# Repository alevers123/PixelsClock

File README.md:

# PixelsClock
Seven Segment LED Clock made from Neo Pixels

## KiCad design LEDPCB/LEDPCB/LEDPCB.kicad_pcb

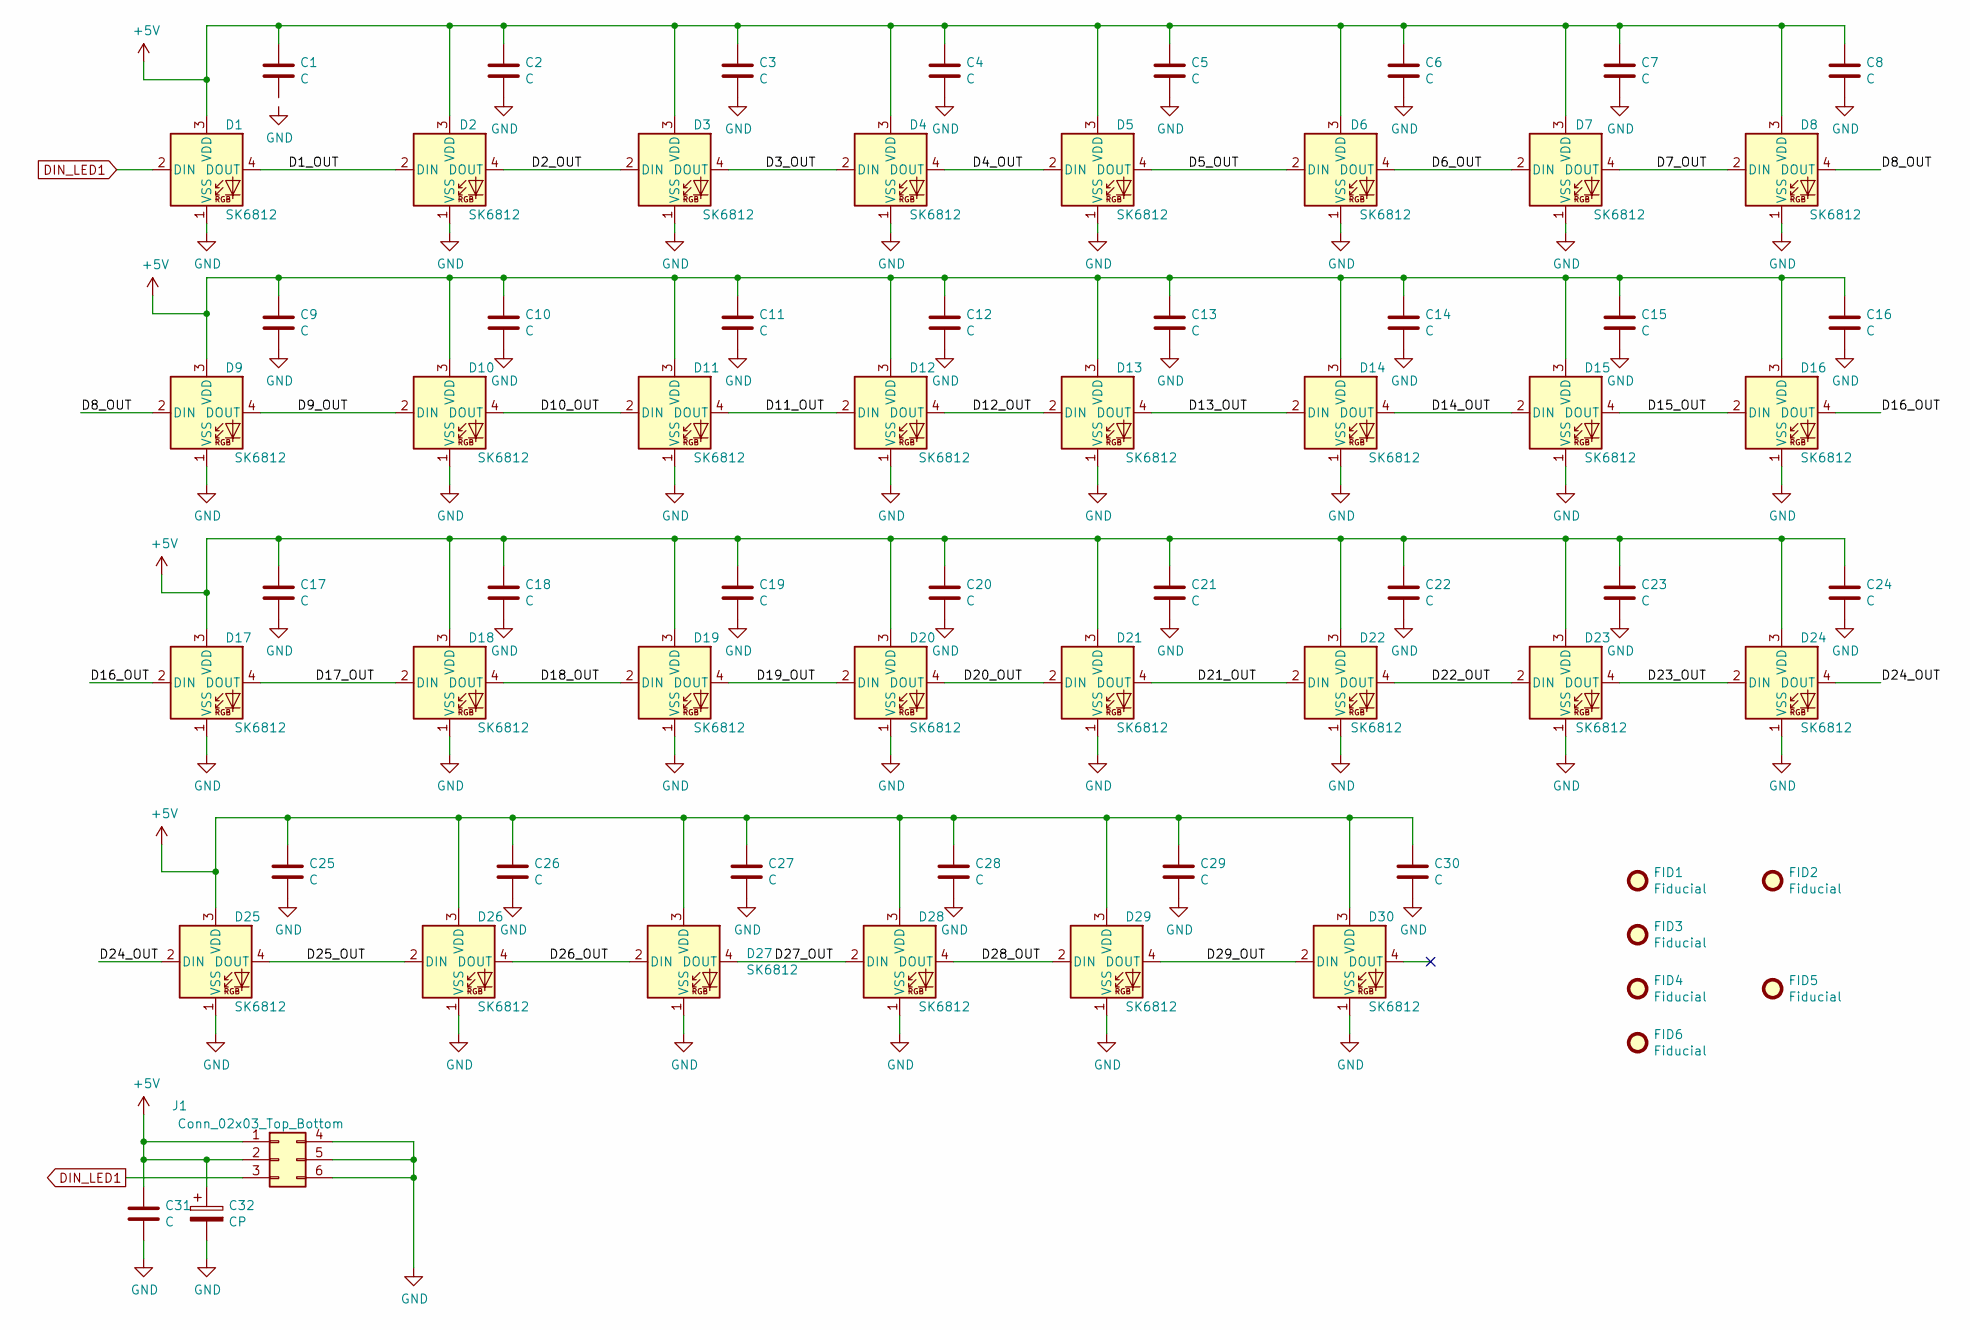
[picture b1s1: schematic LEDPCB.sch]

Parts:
C1, C2, C3, C4, C5, C6, C7, C8, C9, C10, C11, C12, C13, C14, C15, C16, C17, C18, C19, C20, C21, C22, C23, C24, C25, C26, C27, C28, C29, C30: C; C_0402_1005Metric
C31: C; C_1206_3216Metric
C32: CP; CP_EIA-6032-28_Kemet-C
D1, D2, D3, D4, D5, D6, D7, D8, D9, D10, D11, D12, D13, D14, D15, D16, D17, D18, D19, D20, D21, D22, D23, D24, D25, D26, D27, D28, D29, D30: SK6812; LED_SK6812_PLCC4_5.0x5.0mm_P3.2mm
FID1, FID2, FID3, FID4, FID5, FID6: Fiducial; Fiducial_1mm_Mask2mm
J1: Conn_02x03_Top_Bottom; PinHeader_2x03_P1.00mm_Vertical_SMD

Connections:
+5V: C1.1, C2.1, C3.1, C4.1, C5.1, C6.1, C7.1, C8.1, C9.1, C10.1, C11.1, C12.1, C13.1, C14.1, C15.1, C16.1, C17.1, C18.1, C19.1, C20.1, C21.1, C22.1, C23.1, C24.1, C25.1, C26.1, C27.1, C28.1, C29.1, C30.1, C31.1, C32.1, D1.3 (VDD), D2.3 (VDD), D3.3 (VDD), D4.3 (VDD), D5.3 (VDD), D6.3 (VDD), D7.3 (VDD), D8.3 (VDD), D9.3 (VDD), D10.3 (VDD), D11.3 (VDD), D12.3 (VDD), D13.3 (VDD), D14.3 (VDD), D15.3 (VDD), D16.3 (VDD), D17.3 (VDD), D18.3 (VDD), D19.3 (VDD), D20.3 (VDD), D21.3 (VDD), D22.3 (VDD), D23.3 (VDD), D24.3 (VDD), D25.3 (VDD), D26.3 (VDD), D27.3 (VDD), D28.3 (VDD), D29.3 (VDD), D30.3 (VDD), J1.1, J1.2
/D1_OUT: D1.4 (DOUT), D2.2 (DIN)
/D2_OUT: D2.4 (DOUT), D3.2 (DIN)
/D3_OUT: D3.4 (DOUT), D4.2 (DIN)
/D4_OUT: D4.4 (DOUT), D5.2 (DIN)
/D5_OUT: D5.4 (DOUT), D6.2 (DIN)
/D6_OUT: D6.4 (DOUT), D7.2 (DIN)
/D7_OUT: D7.4 (DOUT), D8.2 (DIN)
/D8_OUT: D8.4 (DOUT), D9.2 (DIN)
/D9_OUT: D9.4 (DOUT), D10.2 (DIN)
/D10_OUT: D10.4 (DOUT), D11.2 (DIN)
/D11_OUT: D11.4 (DOUT), D12.2 (DIN)
/D12_OUT: D12.4 (DOUT), D13.2 (DIN)
/D13_OUT: D13.4 (DOUT), D14.2 (DIN)
/D14_OUT: D14.4 (DOUT), D15.2 (DIN)
/D15_OUT: D15.4 (DOUT), D16.2 (DIN)
/D16_OUT: D16.4 (DOUT), D17.2 (DIN)
/D17_OUT: D17.4 (DOUT), D18.2 (DIN)
/D18_OUT: D18.4 (DOUT), D19.2 (DIN)
/D19_OUT: D19.4 (DOUT), D20.2 (DIN)
/D20_OUT: D20.4 (DOUT), D21.2 (DIN)
/D21_OUT: D21.4 (DOUT), D22.2 (DIN)
/D22_OUT: D22.4 (DOUT), D23.2 (DIN)
/D23_OUT: D23.4 (DOUT), D24.2 (DIN)
/D24_OUT: D24.4 (DOUT), D25.2 (DIN)
/D25_OUT: D25.4 (DOUT), D26.2 (DIN)
/D26_OUT: D26.4 (DOUT), D27.2 (DIN)
/D27_OUT: D27.4 (DOUT), D28.2 (DIN)
/D28_OUT: D28.4 (DOUT), D29.2 (DIN)
/D29_OUT: D29.4 (DOUT), D30.2 (DIN)
DIN_LED1: D1.2 (DIN), J1.3
GND: C2.2, C3.2, C4.2, C5.2, C6.2, C7.2, C8.2, C9.2, C10.2, C11.2, C12.2, C13.2, C14.2, C15.2, C16.2, C17.2, C18.2, C19.2, C20.2, C21.2, C22.2, C23.2, C24.2, C25.2, C26.2, C27.2, C28.2, C29.2, C30.2, C31.2, C32.2, D1.1 (VSS), D2.1 (VSS), D3.1 (VSS), D4.1 (VSS), D5.1 (VSS), D6.1 (VSS), D7.1 (VSS), D8.1 (VSS), D9.1 (VSS), D10.1 (VSS), D11.1 (VSS), D12.1 (VSS), D13.1 (VSS), D14.1 (VSS), D15.1 (VSS), D16.1 (VSS), D17.1 (VSS), D18.1 (VSS), D19.1 (VSS), D20.1 (VSS), D21.1 (VSS), D22.1 (VSS), D23.1 (VSS), D24.1 (VSS), D25.1 (VSS), D26.1 (VSS), D27.1 (VSS), D28.1 (VSS), D29.1 (VSS), D30.1 (VSS), J1.4, J1.5, J1.6

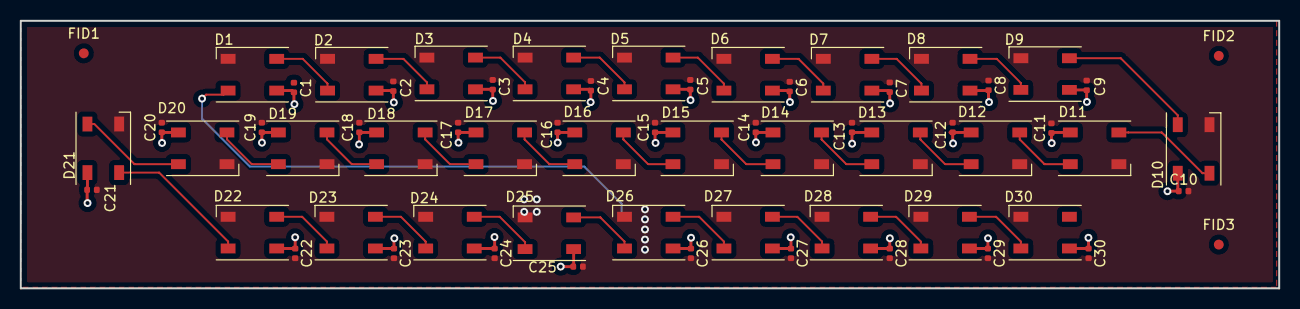
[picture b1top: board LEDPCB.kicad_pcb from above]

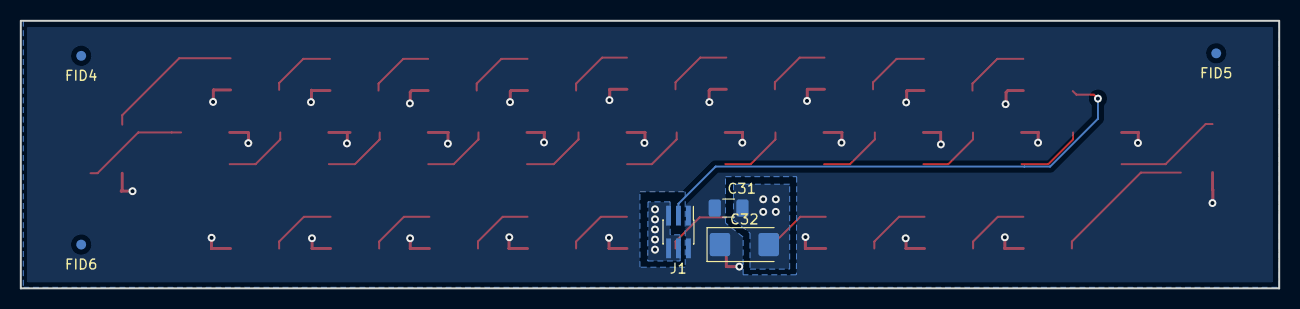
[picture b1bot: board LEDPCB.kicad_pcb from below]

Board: 2 copper layers, 127.0 x 27.0 mm, 69 parts (6 on the bottom side), 32 nets.

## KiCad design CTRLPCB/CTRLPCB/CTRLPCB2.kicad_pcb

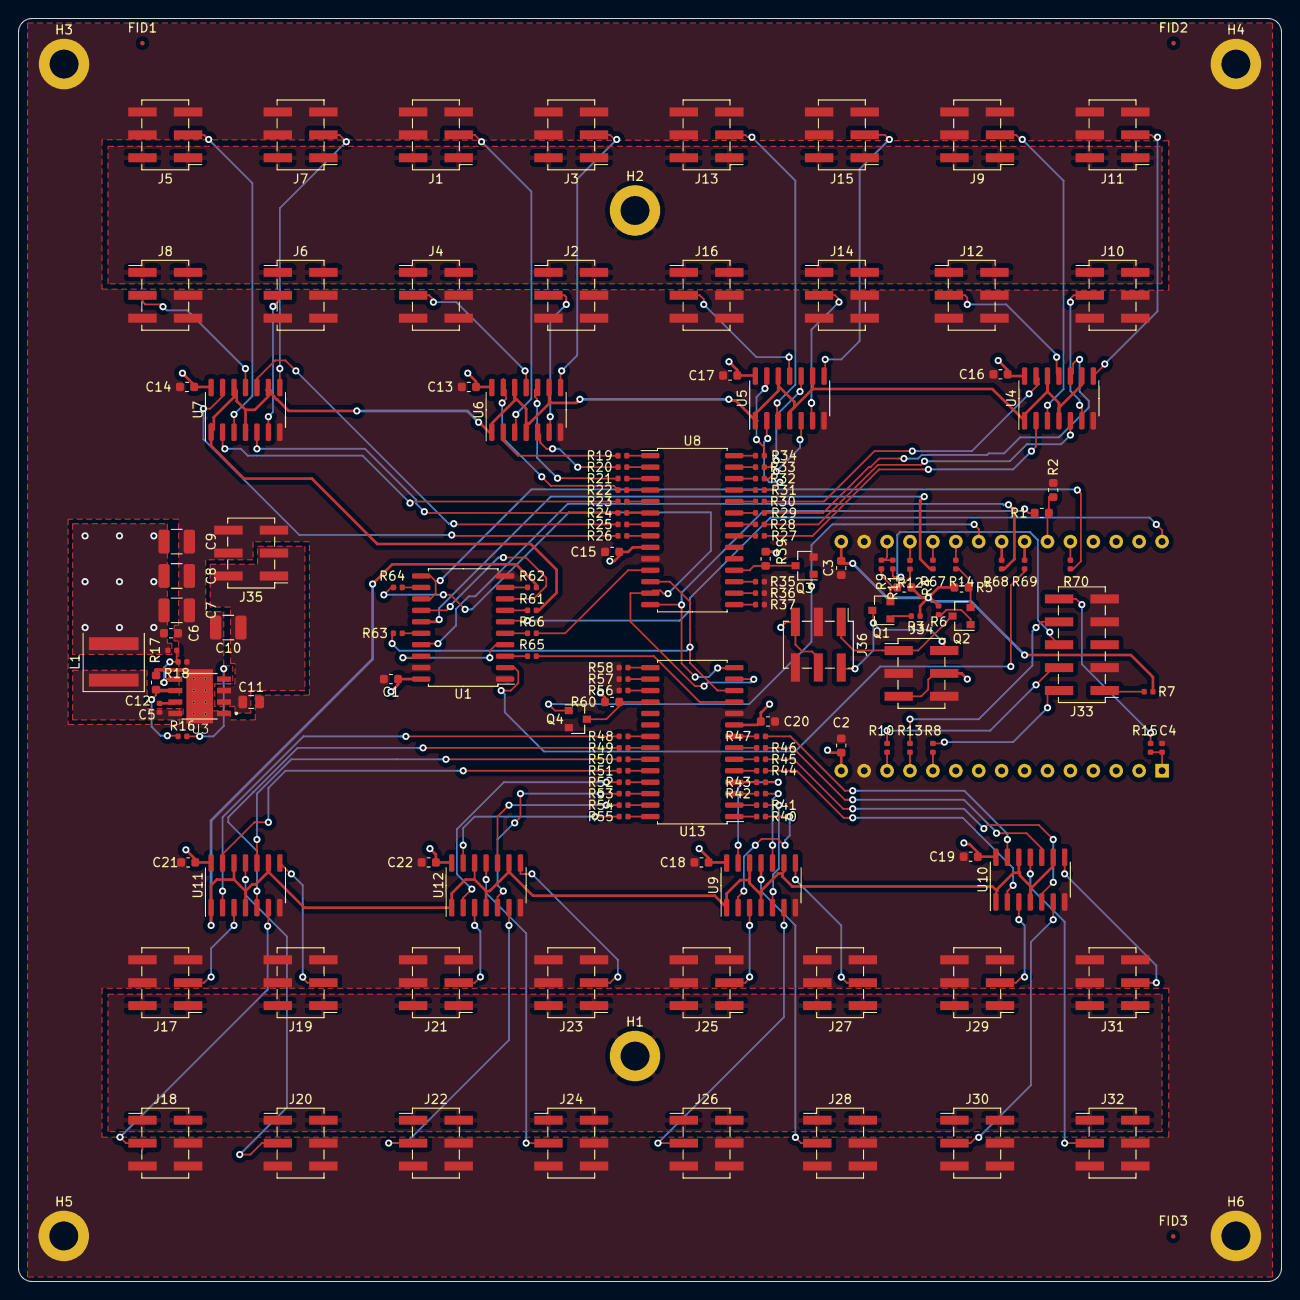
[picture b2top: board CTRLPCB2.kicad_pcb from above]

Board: 2 copper layers, 140.0 x 140.0 mm, 153 parts (1 on the bottom side), 160 nets.

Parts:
C1, C2, C3, C15, C20: C; C_0603_1608Metric
C4: C; C_0402_1005Metric
C5: 100nF; C_0402_1005Metric
C6: 100nF; C_0603_1608Metric
C7, C8, C9: C; C_1210_3225Metric
C10: 10u; C_1210_3225Metric
C11: 220n; C_0805_2012Metric
C12: 1u; C_0603_1608Metric
C13, C14, C16, C17, C18, C19, C21, C22: 100n; C_0603_1608Metric
FID1, FID2, FID3: Fiducial; Fiducial_0.5mm_Mask1.5mm
H1, H2, H3, H4, H5, H6: MountingHole_Pad; MountingHole_3.2mm_M3_DIN965_Pad
J1, J2, J3, J4, J5, J6, J7, J8, J9, J10, J11, J12, J13, J14, J15, J16, J17, J18, J19, J20, J21, J22, J23, J24, J25, J26, J27, J28, J29, J30, J31, J32, J34, J35, J36: Conn_02x03_Top_Bottom; PinHeader_2x03_P2.54mm_Vertical_SMD
J33: Conn_02x05_Odd_Even; PinHeader_2x05_P2.54mm_Vertical_SMD
L1: 10u; L_Coilcraft_XAL60xx_6.36x6.56mm
Q1, Q2, Q3, Q4: Q_NMOS_GSD; SOT-23
R1: 510R; R_0603_1608Metric
R2, R39, R60: 1k; R_0603_1608Metric
R3, R6, R7, R8, R9, R10, R11, R12, R13, R14, R15, R20, R21, R22, R23, R24, R25, R26, R27, R28, R29, R30, R31, R32, R33, R34, R36, R37, R41, R42, R43, R44, R45, R46, R47, R48, R49, R50, R51, R52, R53, R54, R55, R57, R58, R61, R62, R63, R64, R65, R66, R67, R68, R69, R70: 33R; R_0402_1005Metric
R4, R5: 2k; R_0603_1608Metric
R16, R17: 100k; R_0402_1005Metric
R18: 24.9k; R_0402_1005Metric
R19, R35, R40, R56: 33; R_0402_1005Metric
U1: 74HCT240; SOIC-20W_7.5x12.8mm_P1.27mm
U2: ESP32_DevKit_V1_DOIT; esp32_devkit_v1_doit
U3: LMR33630ADDA; NOPB
U4, U5, U6, U7, U9, U10, U11, U12: 74HC00; SOIC-14_3.9x8.7mm_P1.27mm
U8, U13: MCP23S17_SO; SOIC-28W_7.5x17.9mm_P1.27mm

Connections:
+3V3: C3.2, R3.1, R4.1, R5.1, R6.1, R7.2, U2.16
+5V: C1.1, C2.1, C6.1, C7.1, C8.1, C9.1, C13.1, C14.1, C15.1, C16.1, C17.1, C18.1, C19.1, C20.1, C21.1, C22.1, J34.4, J34.5, J36.4, J36.5, L1.2, R17.1, R39.1, R60.1, U1.20, U2.15, U4.14, U5.14, U6.14, U7.14, U8.9, U9.14, U10.14, U11.14, U12.14, U13.9
+24V: C10.1, C11.1, J35.1, J35.2, J35.3, U3.2, U3.3
/+5V_HIGH_POWER: H2.1, J1.1, J1.2, J2.1, J2.2, J3.1, J3.2, J4.1, J4.2, J5.1, J5.2, J6.1, J6.2, J7.1, J7.2, J8.1, J8.2, J9.1, J9.2, J10.1, J10.2, J11.1, J11.2, J12.1, J12.2, J13.1, J13.2, J14.1, J14.2, J15.1, J15.2, J16.1, J16.2
/+5V_HIGH_POWER_2: H1.1, J17.1, J17.2, J18.1, J18.2, J19.1, J19.2, J20.1, J20.2, J21.1, J21.2, J22.1, J22.2, J23.1, J23.2, J24.1, J24.2, J25.1, J25.2, J26.1, J26.2, J27.1, J27.2, J28.1, J28.2, J29.1, J29.2, J30.1, J30.2, J31.1, J31.2, J32.1, J32.2
/CS0: R68.1, U1.17
/CS0_INV_LEV: R65.2, U1.3
/CS0_INV_LEV_E: R65.1, U13.11
/CS1: R67.1, U1.15
/CS2_INV_LEV: R66.2, U1.5
/CS2_INV_LEV_E: R66.1, U8.11
/GPIO2: R12.2, U2.19
/GPIO4: R67.2, U2.20
/GPIO5: R68.2, U2.23
/GPIO12: R13.2, U2.12
/GPIO13: R10.2, U2.13
/GPIO14: R8.2, U2.11
/GPIO15: R9.2, R11.2, U2.18
/GPIO16: R14.2, U2.21
/GPIO18: R69.2, U2.24
/GPIO21: R70.2, U2.26
/I2C_SCL: Q2.2, R5.2, R14.1
/I2C_SDA: Q1.2, R4.2, R9.1, R12.1
/I2S_SK6812: R70.1, U1.11, U1.13
/I2S_SK6812_INV_LEV_1: R61.2, U1.7
/I2S_SK6812_INV_LEV_1_E: R61.1, U4.1, U4.4, U4.9, U4.12, U5.1, U5.4, U5.9, U5.12, U6.1, U6.4, U6.9, U6.12, U7.1, U7.4, U7.9, U7.12
/I2S_SK6812_INV_LEV_2: R62.2, U1.9
/I2S_SK6812_INV_LEV_2_E: R62.1, U9.1, U9.4, U9.9, U9.12, U10.1, U10.4, U10.9, U10.12, U11.1, U11.4, U11.9, U11.12, U12.1, U12.4, U12.9, U12.12
/MISO: R1.1, U8.14, U13.14
/MISO_LEV: R1.2, R2.1, U2.25
/MOSI: U1.6, U2.30
/MOSI_INV_LEV: U1.8, U1.14
/MOSI_LEV: R64.2, U1.12
/RESET: J33.10, R15.2
/SCK: R69.1, U1.2
/SCK_INV_LEV: U1.4, U1.18
/SCK_LEV: R63.2, U1.16
/SCK_LEV_E: R63.1, U8.12, U13.12
/SEG_BUS2_0: J17.3, U11.3
/SEG_BUS2_1: J18.3, U11.6
/SEG_BUS2_2: J19.3, U11.8
/SEG_BUS2_3: J20.3, U11.11
/SEG_BUS2_4: J21.3, U12.3
/SEG_BUS2_5: J22.3, U12.6
/SEG_BUS2_6: J23.3, U12.8
/SEG_BUS2_7: J24.3, U12.11
/SEG_BUS2_8: J25.3, U9.3
/SEG_BUS2_9: J26.3, U9.6
/SEG_BUS2_10: J27.3, U9.8
/SEG_BUS2_11: J28.3, U9.11
/SEG_BUS2_12: J29.3, U10.3
/SEG_BUS2_13: J30.3, U10.6
/SEG_BUS2_14: J31.3, U10.8
/SEG_BUS2_15: J32.3, U10.11
/SEG_BUS_0: J1.3, U6.3
/SEG_BUS_1: J2.3, U6.6
/SEG_BUS_2: J3.3, U6.8
/SEG_BUS_3: J4.3, U6.11
/SEG_BUS_4: J5.3, U7.3
/SEG_BUS_5: J6.3, U7.6
/SEG_BUS_6: J7.3, U7.8
/SEG_BUS_7: J8.3, U7.11
/SEG_BUS_8: J9.3, U4.3
/SEG_BUS_9: J10.3, U4.6
/SEG_BUS_10: J11.3, U4.8
/SEG_BUS_11: J12.3, U4.11
/SEG_BUS_12: J13.3, U5.3
/SEG_BUS_13: J14.3, U5.6
/SEG_BUS_14: J15.3, U5.8
/SEG_BUS_15: J16.3, U5.11
/Sheet5FDBBAA1_2/MOSI: R64.1, U8.13, U13.13
/Sheet5FDBBAA1_2/PA0: R19.2, U8.1
/Sheet5FDBBAA1_2/PA0_E: R19.1, U6.2
/Sheet5FDBBAA1_2/PA1: R20.2, U8.2
/Sheet5FDBBAA1_2/PA1_E: R20.1, U6.5
/Sheet5FDBBAA1_2/PA2: R21.2, U8.3
/Sheet5FDBBAA1_2/PA2_E: R21.1, U6.10
/Sheet5FDBBAA1_2/PA3: R22.2, U8.4
/Sheet5FDBBAA1_2/PA3_E: R22.1, U6.13
/Sheet5FDBBAA1_2/PA4: R23.2, U8.5
/Sheet5FDBBAA1_2/PA4_E: R23.1, U7.2
/Sheet5FDBBAA1_2/PA5: R24.2, U8.6
/Sheet5FDBBAA1_2/PA5_E: R24.1, U7.5
/Sheet5FDBBAA1_2/PA6: R25.2, U8.7
/Sheet5FDBBAA1_2/PA6_E: R25.1, U7.10
/Sheet5FDBBAA1_2/PA7: R26.2, U8.8
/Sheet5FDBBAA1_2/PA7_E: R26.1, U7.13
/Sheet5FDBBAA1_2/PB0: R27.2, U8.21
/Sheet5FDBBAA1_2/PB0_E: R27.1, U4.2
/Sheet5FDBBAA1_2/PB1: R28.2, U8.22
/Sheet5FDBBAA1_2/PB1_E: R28.1, U4.5
/Sheet5FDBBAA1_2/PB2: R29.2, U8.23
/Sheet5FDBBAA1_2/PB2_E: R29.1, U4.10
/Sheet5FDBBAA1_2/PB3: R30.2, U8.24
/Sheet5FDBBAA1_2/PB3_E: R30.1, U4.13
/Sheet5FDBBAA1_2/PB4: R31.2, U8.25
/Sheet5FDBBAA1_2/PB4_E: R31.1, U5.2
/Sheet5FDBBAA1_2/PB5: R32.2, U8.26
/Sheet5FDBBAA1_2/PB5_E: R32.1, U5.5
/Sheet5FDBBAA1_2/PB6: R33.2, U8.27
/Sheet5FDBBAA1_2/PB6_E: R33.1, U5.10
/Sheet5FDBBAA1_2/PB7: R34.2, U8.28
/Sheet5FDBBAA1_2/PB7_E: R34.1, U5.13
/Sheet5FDBBAA1_2/RESET: Q3.1, Q4.1, U2.22
/TCLK: J33.4, R10.1
/TDI: J33.8, R13.1
/TDO: J33.6, R11.1
/TMS: J33.2, R8.1
/sheet5FF17740/PA0: R48.2, U13.21
/sheet5FF17740/PA0_E: R48.1, U11.2
/sheet5FF17740/PA1: R49.2, U13.22
/sheet5FF17740/PA1_E: R49.1, U11.5
/sheet5FF17740/PA2: R50.2, U13.23
/sheet5FF17740/PA2_E: R50.1, U11.10
/sheet5FF17740/PA3: R51.2, U13.24
/sheet5FF17740/PA3_E: R51.1, U11.13
/sheet5FF17740/PA4: R52.2, U13.25
/sheet5FF17740/PA4_E: R52.1, U12.2
/sheet5FF17740/PA5: R53.2, U13.26
/sheet5FF17740/PA5_E: R53.1, U12.5
/sheet5FF17740/PA6: R54.2, U13.27
/sheet5FF17740/PA6_E: R54.1, U12.10
/sheet5FF17740/PA7: R55.2, U13.28
/sheet5FF17740/PA7_E: R55.1, U12.13
/sheet5FF17740/PB0: R40.2, U13.1
/sheet5FF17740/PB0_E: R40.1, U9.2
/sheet5FF17740/PB1: R41.2, U13.2
/sheet5FF17740/PB1_E: R41.1, U9.5
/sheet5FF17740/PB2: R42.2, U13.3
/sheet5FF17740/PB2_E: R42.1, U9.10
/sheet5FF17740/PB3: R43.2, U13.4
/sheet5FF17740/PB3_E: R43.1, U9.13
/sheet5FF17740/PB4: R44.2, U13.5
/sheet5FF17740/PB4_E: R44.1, U10.2
/sheet5FF17740/PB5: R45.2, U13.6
/sheet5FF17740/PB5_E: R45.1, U10.5
/sheet5FF17740/PB6: R46.2, U13.7
/sheet5FF17740/PB6_E: R46.1, U10.10
/sheet5FF17740/PB7: R47.2, U13.8
/sheet5FF17740/PB7_E: R47.1, U10.13
GND: C1.2, C2.2, C3.1, C4.1, C6.2, C7.2, C8.2, C9.2, C10.2, C11.2, C12.2, C13.2, C14.2, C15.2, C16.2, C17.2, C18.2, C19.2, C20.2, C21.2, C22.2, H3.1, H4.1, H5.1, H6.1, J1.4, J1.5, J1.6, J2.4, J2.5, J2.6, J3.4, J3.5, J3.6, J4.4, J4.5, J4.6, J5.4, J5.5, J5.6, J6.4, J6.5, J6.6, J7.4, J7.5, J7.6, J8.4, J8.5, J8.6, J9.4, J9.5, J9.6, J10.4, J10.5, J10.6, J11.4, J11.5, J11.6, J12.4, J12.5, J12.6, J13.4, J13.5, J13.6, J14.4, J14.5, J14.6, J15.4, J15.5, J15.6, J16.4, J16.5, J16.6, J17.4, J17.5, J17.6, J18.4, J18.5, J18.6, J19.4, J19.5, J19.6, J20.4, J20.5, J20.6, J21.4, J21.5, J21.6, J22.4, J22.5, J22.6, J23.4, J23.5, J23.6, J24.4, J24.5, J24.6, J25.4, J25.5, J25.6, J26.4, J26.5, J26.6, J27.4, J27.5, J27.6, J28.4, J28.5, J28.6, J29.4, J29.5, J29.6, J30.4, J30.5, J30.6, J31.4, J31.5, J31.6, J32.4, J32.5, J32.6, J33.3, J33.7, J33.9, J34.3, J34.6, J35.4, J35.5, J35.6, J36.3, J36.6, Q3.2, Q4.2, R2.2, R18.2, R35.2, R36.2, R37.2, R56.2, R57.2, R58.2, U1.1, U1.10, U1.19, U2.14, U2.17, U3.1, U3.9, U4.7, U5.7, U6.7, U7.7, U8.10, U9.7, U10.7, U11.7, U12.7, U13.10
unnamed: C4.2, R15.1, U2.1
unnamed: C5.1, L1.1, U3.8
unnamed: C5.2, U3.7
unnamed: C12.1, R16.1, U3.6
unnamed: J33.1, R7.1
unnamed: J34.1, J36.1, Q2.3
unnamed: J34.2, J36.2, Q1.3
unnamed: Q1.1, R3.2
unnamed: Q2.1, R6.2
unnamed: Q3.3, R39.2, U8.18
unnamed: Q4.3, R60.2, U13.18
unnamed: R16.2, U3.4
unnamed: R17.2, R18.1, U3.5
unnamed: R35.1, U8.17
unnamed: R36.1, U8.16
unnamed: R37.1, U8.15
unnamed: R56.1, U13.17
unnamed: R57.1, U13.16
unnamed: R58.1, U13.15
